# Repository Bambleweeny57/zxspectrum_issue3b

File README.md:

# **ZX Spectrum Issue 3B — KiCad Reconstruction**

A faithful KiCad recreation of the **Sinclair ZX Spectrum Issue 3B motherboard**, reconstructed from original Gerber data and fully validated through multiple successful builds.  
This project preserves the 3B layout in an editable, open format and includes several companion PCBs designed to modernise, repair, or enhance the original Spectrum hardware.

---

## 🧭 Project Purpose

The aim of this repository is to provide a clean, accurate, and reproducible version of the Issue 3B board for:

- Restoring original machines  
- Building new units from scratch  
- Hardware experimentation and modding  
- Long‑term preservation of Sinclair’s design  

All PCBs included here have been **physically manufactured and tested**.

---

## 🛠️ Included PCBs

### **✔️ Issue 3B Motherboard (KiCad Reconstruction)**  
A complete KiCad recreation of the original Issue 3B board.

- Rebuilt directly from Gerbers  
- Trace‑accurate routing  
- Multiple boards assembled and working perfectly  
- Compatible with original components and modern equivalents  

---

### **✔️ Coil Replacement PCB**  
A compact, reliable drop‑in replacement for the original Spectrum coil assembly.

- Tested and working  
- More consistent output than ageing originals  
- Builder‑friendly footprint and assembly  

---

### **✔️ Composite Mod PCB (Internal Modulator Replacement)**  
This PCB is designed to **fit inside the original RF modulator can**, replacing the internal circuitry while keeping the metal can for authenticity.

- Produces a clean composite video output  
- Eliminates RF noise and modulator‑related issues  
- Fully validated on real hardware  
- Ideal for restorations where the external appearance should remain original  

---

### **✔️ Composite Modulator Replacement PCB**  
A full PCB replacement for the RF modulator can itself.

- Suitable for new builds or heavily damaged modulators  
- Provides modern composite output in a clean, serviceable form  
- Tested and working  

---

## 🧩 Issue 3B Schematic (Work in Progress)

A full schematic for the **Issue 3B motherboard** is currently being drafted.  
It lives in the main **`/src`** directory alongside the KiCad PCB project and is already far enough along to be useful for reference, verification, and troubleshooting.

- Based on the reconstructed PCB  
- Continuously refined as traces and nets are validated  
- Intended to become a complete, accurate representation of the 3B circuitry  
- A PDF export is also included in **`/images`** for quick viewing

This schematic will evolve as the project progresses, but it is already a solid and reliable companion to the board reconstruction.

---

## 📁 Repository Structure

| Path | Description |
|------|-------------|
| `/src` | KiCad project files for the Issue 3B board |
| `/zx_coil` | Coil replacement PCB |
| `/zx_composite_mod` | Composite mod PCB (internal modulator replacement) |
| `/zx_composite_modulator` | Full modulator replacement PCB |
| `README.md` | Project overview |

---

## 🔧 Build Status

All PCBs in this repository have been **successfully manufactured, assembled, and tested**.

| PCB | Status |
|-----|--------|
| Issue 3B Motherboard | ✅ Working |
| Coil Replacement PCB | ✅ Working |
| Composite Mod PCB | ✅ Working |
| Composite Modulator PCB | ✅ Working |

---

## 📐 About the Issue 3B Revision

The Issue 3B is one of the later 48K Spectrum board revisions, featuring:

- Improved manufacturing consistency  
- Minor routing and grounding refinements  
- Updated power regulation layout  
- Compatibility with both early and late ULAs  

This reconstruction preserves the original routing and component placement as closely as possible.

---

## 🤝 Contributing

Contributions that improve accuracy, documentation, or long‑term preservation of the Issue 3B are welcome.  
This includes:

- Verified corrections to the schematic or PCB reconstruction  
- High‑resolution board scans, trace photos, or component placement references  
- Improvements to KiCad symbols, footprints, or net annotations  
- Build reports, troubleshooting notes, or compatibility findings  
- Additional companion PCBs that relate to the 3B ecosystem  

Please open an issue or pull request with clear details so changes can be reviewed and validated against real hardware where possible.

---

## 📜 License

This project is released for educational, preservation, and hobbyist use.  
You are free to study, modify, and build from the files provided.

The original Sinclair ZX Spectrum design remains the intellectual property of its respective rights holders.  
Please respect the historical significance of the original hardware.

---

## 🚀 How to Use This Project

### **Open in KiCad**
```bash
git clone https://github.com/Bambleweeny57/zxspectrum_issue3b

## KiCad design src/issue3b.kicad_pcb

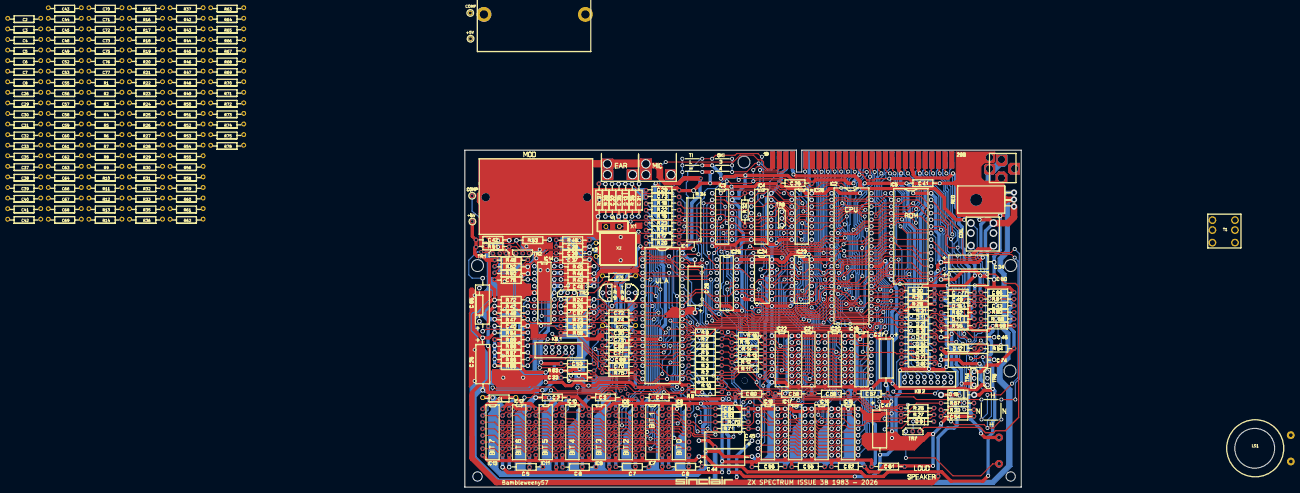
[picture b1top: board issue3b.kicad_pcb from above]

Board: 2 copper layers, 126 parts (0 on the bottom side), 45 nets.

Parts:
C1, C2, C3, C4, C5, C6, C7, C8, C26, C29, C30, C33, C40, C41, C42, C48, C55, C56, C57, C58, C59, C60, C61, C62, C66, C76: 47nF; Passive
C31, C32, C43, C68, C69, C70, C71, C75, C77: 100nF; Passive
C35, C39: 10nF; Passive
C37, C38: 33pF; Passive
C44, C45: 100uF; Passive
C49: 560pF; Passive
C52, C53: 150pF; Passive
C63: 47pF; Passive
C64, C67: 100pF; Passive
C72, C73: 16pF; Passive
LS1: Speaker
R1, R2, R3, R4, R5, R6, R7, R8, R26, R27, R78: 470; Passive
R9, R10, R11, R12, R13, R14, R15, R16: 8k2; Passive
R17, R18, R19, R20, R21, R22, R23: 330; Passive
R24, R73: 1k; Passive
R25: 180; Passive
R28, R29, R30, R35, R49, R65, R66, R67, R68, R69, R72, R74, R75: 10K; Passive
R31: 220K; Passive
R32: 100; Passive
R33, R36: 680; Passive
R37, R42, R45, R46, R47, R56, R58, R63, R76, R77: 1K; Passive
R43: 3K; Passive
R44: 5K1; Passive
R48, R51, R52: 2K2; Passive
R50: 4K7; Passive
R53: 390R; Passive
R54: 100K; Passive
R55: 56; Passive
R59: 1K8; Passive
R60: 68R; Passive
R61, R62, R64: 15; Passive
R70, R71: 220; Passive
T1: Coil
TV1: Modulator
X1: 14Mhz; X1
X2: 4.43Mhz; X2

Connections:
+5V: C26.1, C29.2, C41.1, C55.2, C56.2, C57.2, C58.2, C59.2, C60.2, C61.2, C62.2, C75.2, R9.1, R10.1, R11.1, R12.1, R13.1, R14.1, R15.1, R16.1, R25.1, R28.1, R29.1, R30.1, R31.1, R64.2, R65.1, R66.1, R67.1, R68.1, R69.1, R73.1, R74.2, R75.2, R78.1
+9V: C66.2, T1.4 (SB)
+12V: C5.1, C6.1, C7.1, C8.1, C44.1, R59.2, R62.1
+12VA: C33.2, C45.1, C48.2, C52.2, C53.2, R42.1, R62.2
-5V: C1.1, C2.1, C3.1, C4.1, R54.1
-12VAC: C49.2, T1.3 (SA)
D0: R1.1, R9.2
D1: R2.1, R10.2
D2: R3.1, R11.2
D3: R4.1, R12.2
D4: R5.1, R13.2
D5: R6.1, R14.2
D6: R7.1, R15.2
D7: R8.1, R16.2
GND: C1.2, C2.2, C3.2, C4.2, C5.2, C6.2, C7.2, C8.2, C26.2, C29.1, C30.1, C33.1, C35.1, C37.2, C40.2, C41.2, C42.2, C43.1, C44.2, C45.2, C48.1, C49.1, C55.1, C56.1, C57.1, C58.1, C59.1, C60.1, C61.1, C62.1, C63.2, C64.2, C66.1, C72.2, C73.1, C75.1, C76.1, C77.1, LS1.1, R37.2, R43.1, R46.1, R47.1, R50.1, R52.1, R53.1, R54.2, R56.2, R58.2, R63.2, TV1.3 (GND)
unnamed: C31.1, R35.1
unnamed: C32.2, R36.2
unnamed: C38.1, C39.2, R46.2
unnamed: C38.2, R45.1, X2.2
unnamed: C43.2, R60.2, R61.1
unnamed: C63.1, R71.2
unnamed: C64.1, R70.2
unnamed: C72.1, R44.1, X2.1
unnamed: C73.2, X1.1
unnamed: C32.1, C35.2, R35.2
unnamed: R36.1, R37.1
unnamed: C52.1, R76.2
unnamed: C76.2, R78.2
unnamed: C37.1, R45.2
unnamed: R43.2, R44.2
unnamed: C53.1, R77.2
unnamed: C77.2, R61.2, T1.1 (AA)
unnamed: R48.1, R49.1, R50.2
unnamed: C40.1, C42.1, R49.2, R51.2, R64.1, R72.1, TV1.1 (+5V)
unnamed: C67.2, R24.1
unnamed: R58.1, R59.1
unnamed: C70.1, R75.1
unnamed: C71.1, R77.1
unnamed: C68.1, R74.1
unnamed: C69.1, R76.1
U: C69.2, R56.1
V: C71.2, R63.1
VIDEO: R53.2, TV1.2 (1P)
Y: C68.2, C70.2, R47.2, R48.2
_CK: C67.1, R24.2, R73.2

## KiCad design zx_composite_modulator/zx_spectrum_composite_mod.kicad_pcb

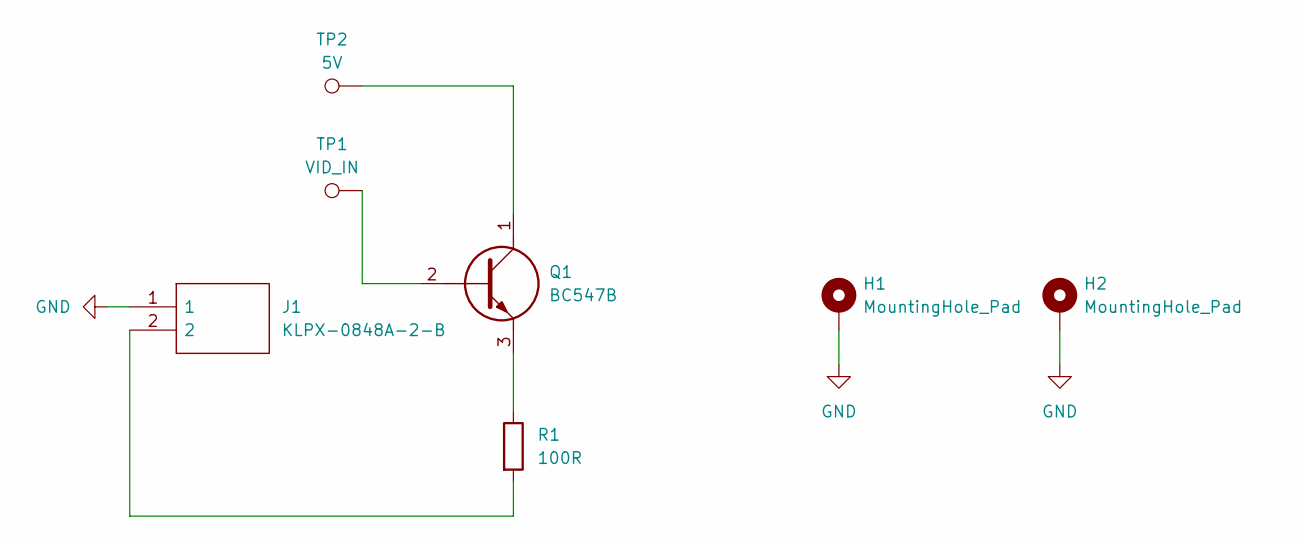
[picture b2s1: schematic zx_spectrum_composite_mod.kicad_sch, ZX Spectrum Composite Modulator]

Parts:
H1, H2: MountingHole_Pad; MountingHole_3.2mm_M3_Pad
J1: KLPX-0848A-2-B; KLPX0848A2B; Mouser Part Number 806-KLPX-0848A-2-B
Q1: BC547B; TO127P419X482X1041-3P; Mouser Part Number 512-BC547B
R1: 100R; R_Axial_DIN0207_L6.3mm_D2.5mm_P10.16mm_Horizontal
TP1: VID_IN; Pin_D0.7mm_L6.5mm_W1.8mm_FlatFork
TP2: 5V; Pin_D0.7mm_L6.5mm_W1.8mm_FlatFork

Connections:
GND: H1.1, H2.1, J1.1
unnamed: J1.2, R1.2
unnamed: Q1.1, TP2.1
unnamed: Q1.2, TP1.1
unnamed: Q1.3, R1.1

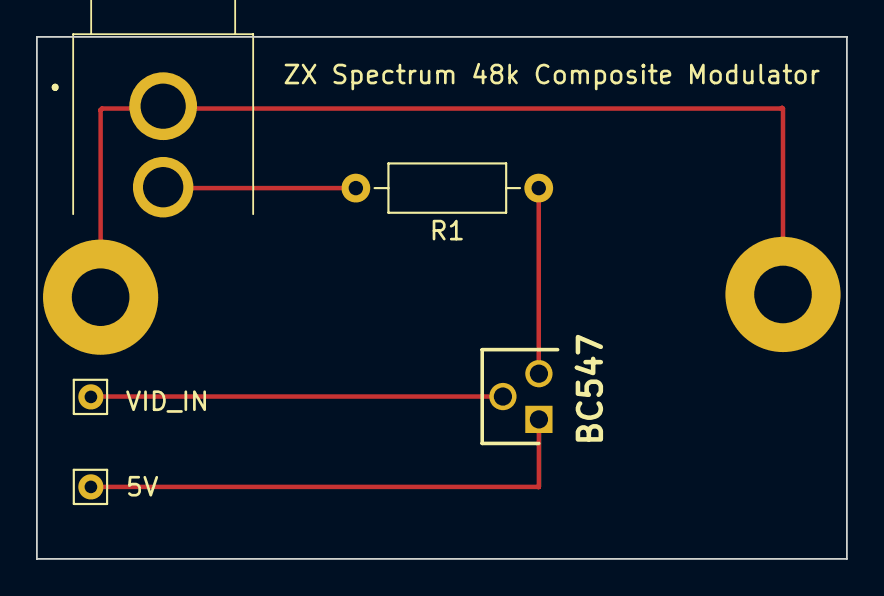
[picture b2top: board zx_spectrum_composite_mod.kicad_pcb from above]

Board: 2 copper layers, 45.0 x 29.0 mm, 7 parts (0 on the bottom side), 5 nets.

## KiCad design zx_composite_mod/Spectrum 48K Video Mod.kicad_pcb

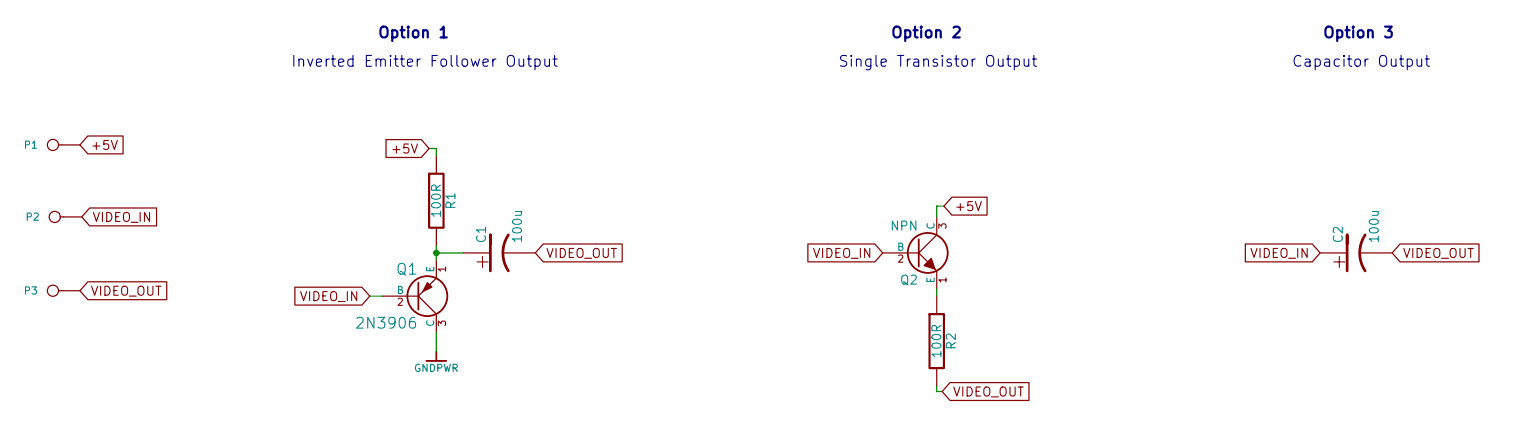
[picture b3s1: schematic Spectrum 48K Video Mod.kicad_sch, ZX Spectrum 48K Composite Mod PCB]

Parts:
C1, C2: 100u; CP_Radial_D7.5mm_P2.50mm
P1, P2, P3: CONN_1; Pin_Header_Straight_1x01_Pitch2.54mm
Q1: 2N3906; TO-92_Inline_Narrow_Oval
Q2: NPN; TO-92_Inline_Narrow_Oval
R1, R2: 100R; R_Axial_DIN0207_L6.3mm_D2.5mm_P10.16mm_Horizontal

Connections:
+5V: P1.1, Q2.3 (C), R1.1
GNDPWR: Q1.3 (C)
unnamed: C1.1, Q1.1 (E), R1.2
unnamed: Q2.1 (E), R2.1
VIDEO_IN: C2.1, P2.1, Q1.2 (B), Q2.2 (B)
VIDEO_OUT: C1.2, C2.2, P3.1, R2.2

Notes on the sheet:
Single Transistor Output
Option 1
Option 2
Option 3
Capacitor Output
Inverted Emitter Follower Output

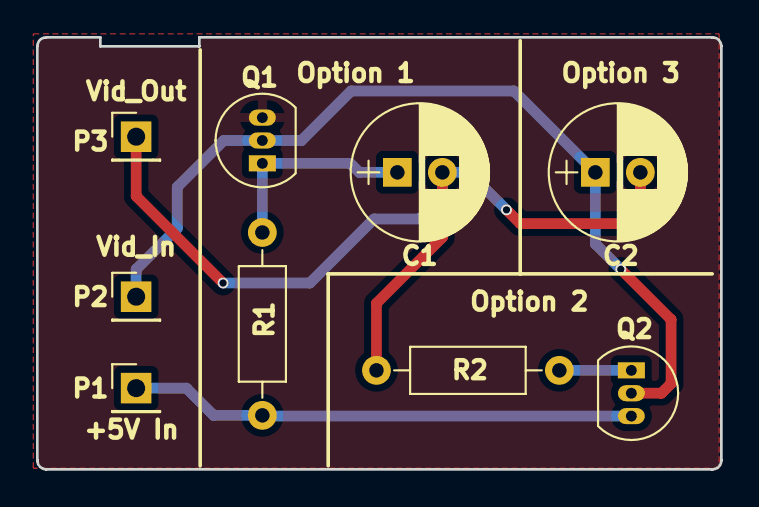
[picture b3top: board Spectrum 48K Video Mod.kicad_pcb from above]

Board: 2 copper layers, 38.0 x 24.0 mm, 9 parts (0 on the bottom side), 5 nets.

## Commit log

2026-01-19 inital push
2026-01-19 change directory
2026-01-20 created gerbers
2026-01-24 new gerbers
2026-01-24 new gerbers for the coil
2026-01-24 added composite mod pcb and single transistor composite modulator replacement
2026-02-06 reduced drill in coil
2026-02-07 Created PDF Component Overlay
2026-02-07 Added an HTML BOM with Silkscreen.
2026-02-08 Added R25 to BOM Started Schematic
2026-02-08 Added Schematic PDF
2026-02-09 Updated schematic re produced schematic pdf
2026-02-09 updated schematic
2026-02-11 added some new footprints
2026-02-11 fixed ibom location
2026-02-28 moved applied footprints
2026-04-10 keyboard added
